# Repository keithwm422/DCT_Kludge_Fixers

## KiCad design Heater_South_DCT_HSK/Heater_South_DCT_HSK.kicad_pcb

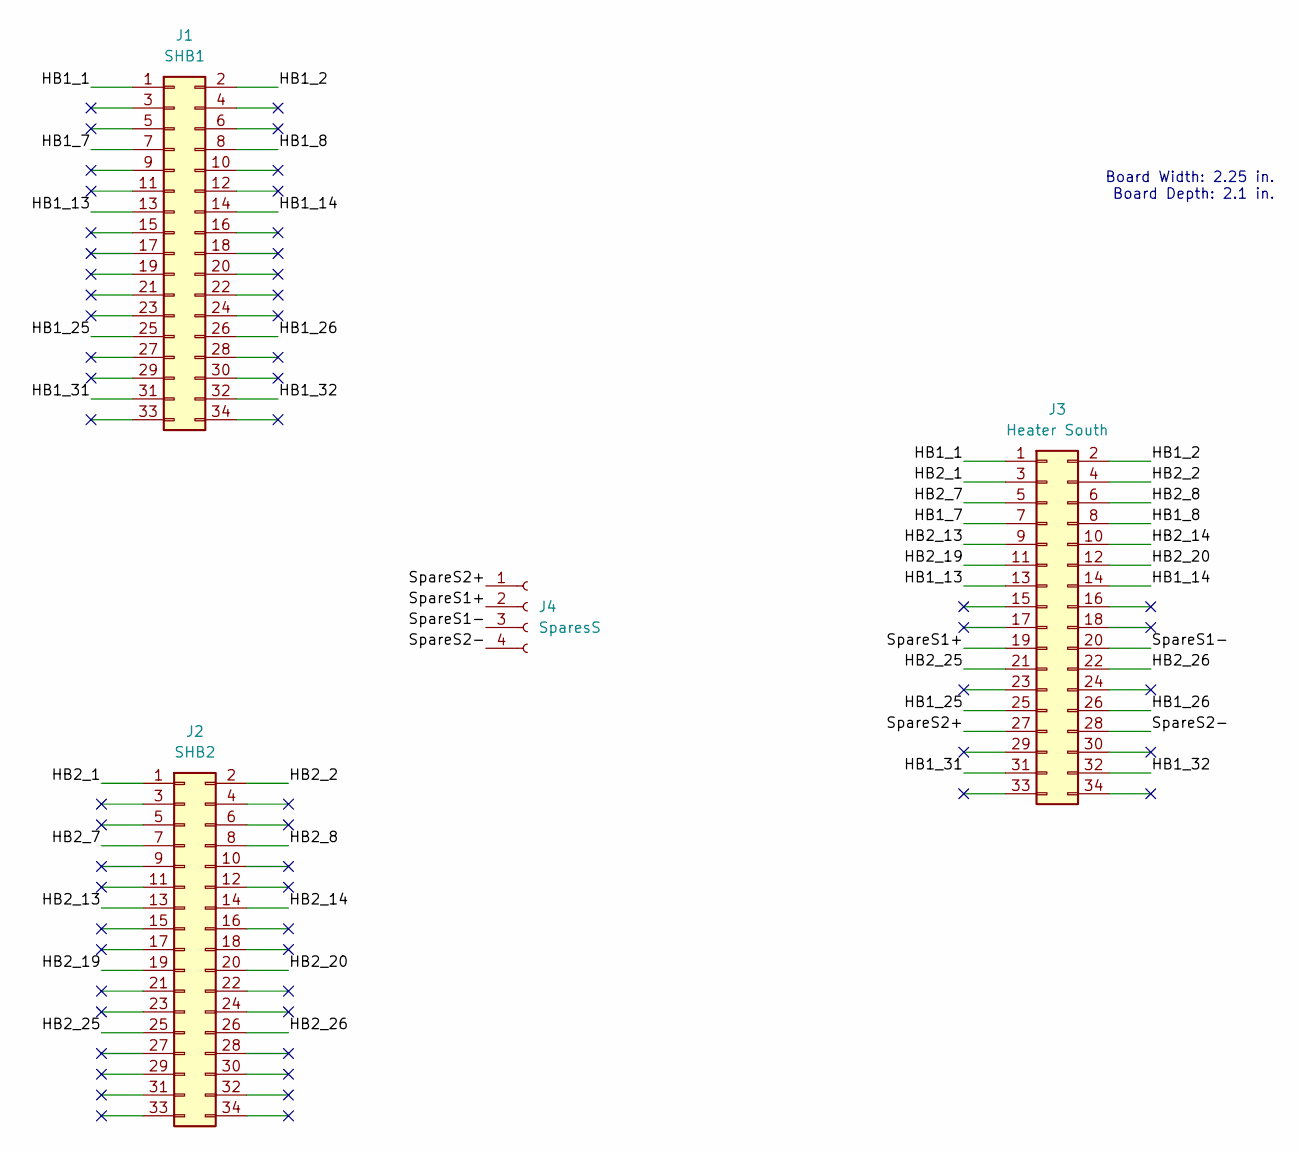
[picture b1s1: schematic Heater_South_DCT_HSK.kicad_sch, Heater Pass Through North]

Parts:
J1: SHB1; HELIX_DCT_ICDconnector34pin_corrected
J2: SHB2; HELIX_DCT_ICDconnector34pin_corrected
J3: Heater South; HELIX_DCT_ICDconnector34pin_corrected
J4: SparesS; Molex_Micro-Fit_3.0_43045-0400_2x02_P3.00mm_Horizontal

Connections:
/HB1_1: J1.1, J3.1
/HB1_2: J1.2, J3.2
/HB1_7: J1.7, J3.7
/HB1_8: J1.8, J3.8
/HB1_13: J1.13, J3.13
/HB1_14: J1.14, J3.14
/HB1_25: J1.25, J3.25
/HB1_26: J1.26, J3.26
/HB1_31: J1.31, J3.31
/HB1_32: J1.32, J3.32
/HB2_1: J2.1, J3.3
/HB2_2: J2.2, J3.4
/HB2_7: J2.7, J3.5
/HB2_8: J2.8, J3.6
/HB2_13: J2.13, J3.9
/HB2_14: J2.14, J3.10
/HB2_19: J2.19, J3.11
/HB2_20: J2.20, J3.12
/HB2_25: J2.25, J3.21
/HB2_26: J2.26, J3.22
/SpareS1+: J3.19, J4.2
/SpareS1-: J3.20, J4.3
/SpareS2+: J3.27, J4.1
/SpareS2-: J3.28, J4.4

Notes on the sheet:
Board Width: 2.25 in. Board Depth: 2.1 in.

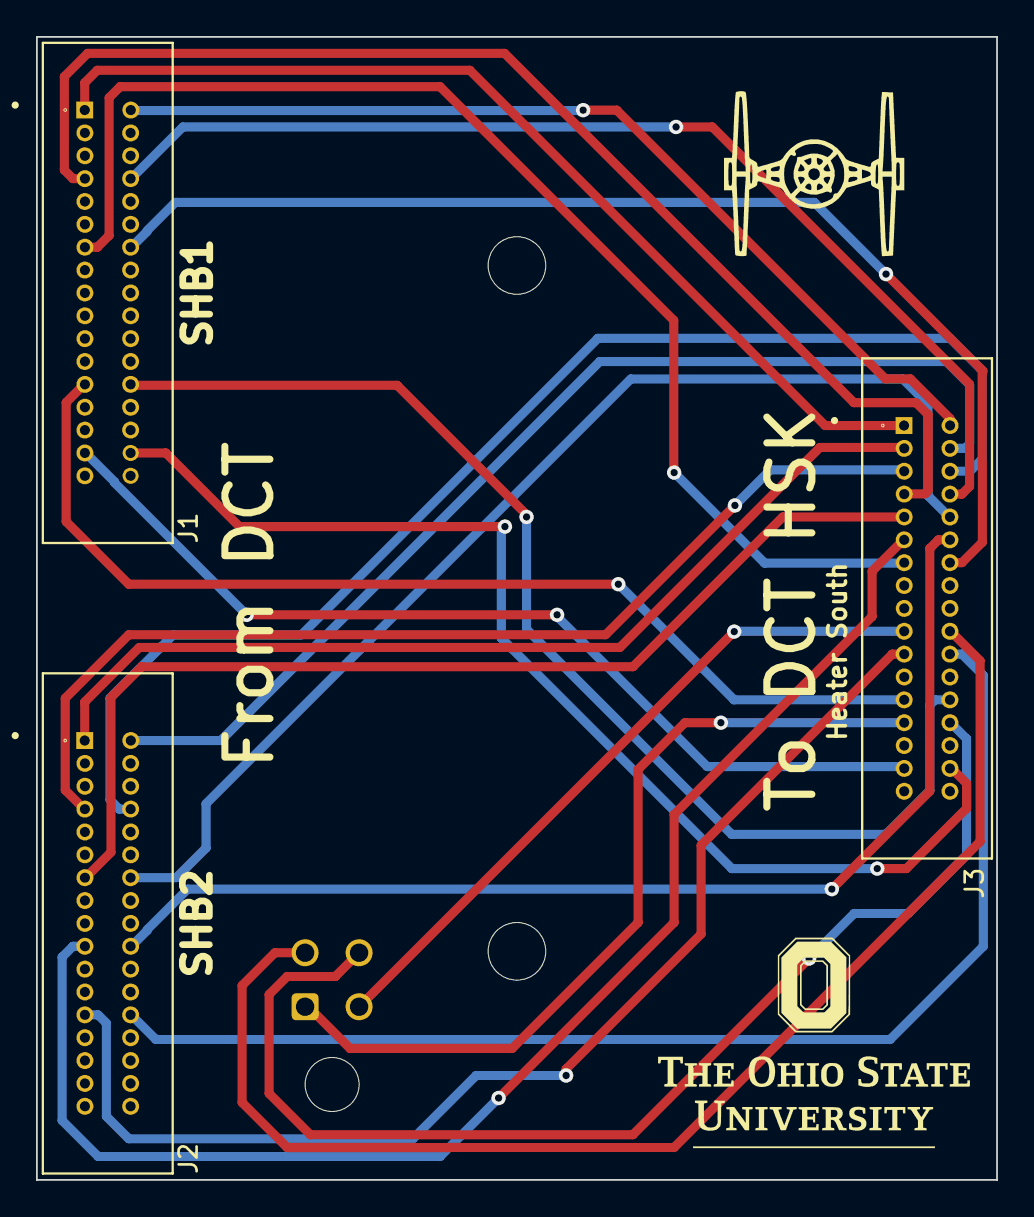
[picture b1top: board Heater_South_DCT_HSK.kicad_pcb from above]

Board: 2 copper layers, 53.3 x 63.5 mm, 4 parts (1 on the bottom side), 24 nets.

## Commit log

2023-10-17 New feedthrough PCBs to access spare heater channels for flowcontroller heaters.
2024-01-15 Files fabbed and tested. These work for the new version of the heater driver PCB.
